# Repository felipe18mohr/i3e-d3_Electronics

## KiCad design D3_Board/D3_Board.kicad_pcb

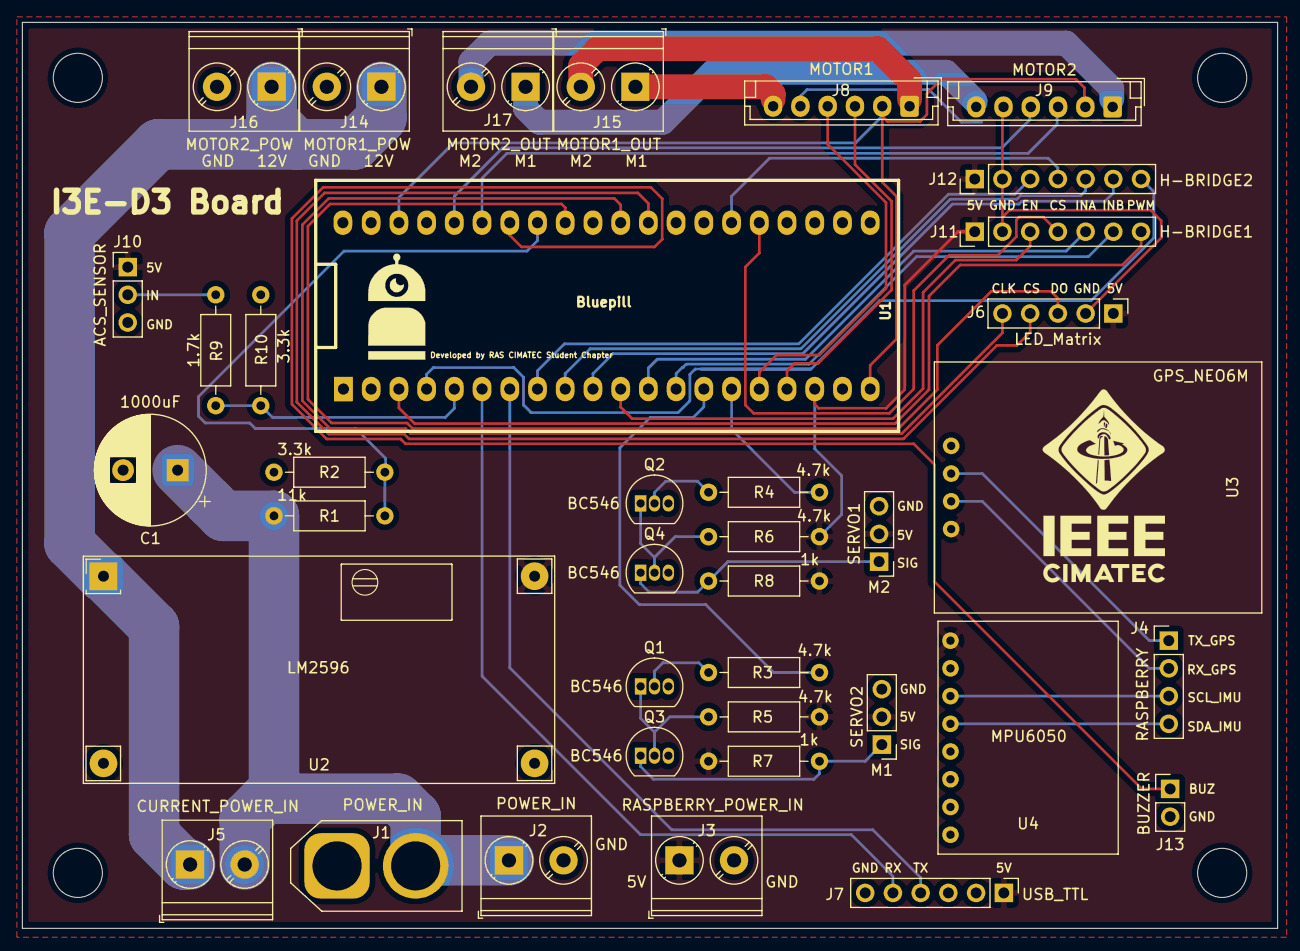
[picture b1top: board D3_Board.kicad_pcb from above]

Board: 2 copper layers, 115.0 x 83.0 mm, 38 parts (0 on the bottom side), 44 nets.

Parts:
C1: 1000uF; CP_Radial_D10.0mm_P5.00mm
J1: POWER_IN; AMASS_XT60-M_1x02_P7.20mm_Vertical
J2: POWER_IN; TerminalBlock_Phoenix_PT-1,5-2-5.0-H_1x02_P5.00mm_Horizontal
J3: RASPBERRY_POWER_IN; TerminalBlock_Phoenix_PT-1,5-2-5.0-H_1x02_P5.00mm_Horizontal
J4: RASPBERRY; PinHeader_1x04_P2.54mm_Vertical
J5: CURRENT_POWER_IN; TerminalBlock_Phoenix_PT-1,5-2-5.0-H_1x02_P5.00mm_Horizontal
J6: LED_Matrix; PinHeader_1x05_P2.54mm_Vertical
J7: USB_TTL; PinHeader_1x06_P2.54mm_Vertical
J8: MOTOR1; JST_EH_B6B-EH-A_1x06_P2.50mm_Vertical
J9: MOTOR2; JST_EH_B6B-EH-A_1x06_P2.50mm_Vertical
J10: ACS_SENSOR; PinHeader_1x03_P2.54mm_Vertical
J11: H-BRIDGE1; PinHeader_1x07_P2.54mm_Vertical
J12: H-BRIDGE2; PinHeader_1x07_P2.54mm_Vertical
J13: BUZZER; PinHeader_1x02_P2.54mm_Vertical
J14: MOTOR1_POW; TerminalBlock_Phoenix_PT-1,5-2-5.0-H_1x02_P5.00mm_Horizontal
J15: MOTOR1_OUT; TerminalBlock_Phoenix_PT-1,5-2-5.0-H_1x02_P5.00mm_Horizontal
J16: MOTOR2_POW; TerminalBlock_Phoenix_PT-1,5-2-5.0-H_1x02_P5.00mm_Horizontal
J17: MOTOR2_OUT; TerminalBlock_Phoenix_PT-1,5-2-5.0-H_1x02_P5.00mm_Horizontal
M1: SERVO2; PinHeader_1x03_P2.54mm_Vertical
M2: SERVO1; PinHeader_1x03_P2.54mm_Vertical
Q1, Q2, Q3, Q4: BC546; TO-92_Inline
R1: 11k; R_Axial_DIN0207_L6.3mm_D2.5mm_P10.16mm_Horizontal
R2, R10: 3.3k; R_Axial_DIN0207_L6.3mm_D2.5mm_P10.16mm_Horizontal
R3, R4, R5, R6: 4.7k; R_Axial_DIN0207_L6.3mm_D2.5mm_P10.16mm_Horizontal
R7, R8: 1k; R_Axial_DIN0207_L6.3mm_D2.5mm_P10.16mm_Horizontal
R9: 1.7k; R_Axial_DIN0207_L6.3mm_D2.5mm_P10.16mm_Horizontal
U1: Bluepill; BluePill_STM32F103C
U2: LM2596; LM2596_module
U3: GPS_NEO6M; GPS_NEO6M_module
U4: MPU6050; MPU6050_module

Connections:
+3V3: J8.2, J9.2, U1.20, U1.38
+5V: J3.1, J6.1, J7.1, J10.1, J11.1, J12.1, M1.2, M2.2, R5.2, R6.2, R7.2, R8.2, U1.18, U2.4, U3.1, U4.1
+12V: J5.1, J14.1, J16.1, U2.1
/ACS: R9.2, R10.1, U1.5
/AVS: R1.2, R2.1, U1.33
/BUZZER: J13.1, U1.34
/CLK_LED: J6.5, U1.30
/CS_LED: J6.4, U1.29
/DOUT_LED: J6.3, U1.32
/ENCODER1_A: J8.4, U1.16
/ENCODER1_B: J8.3, U1.17
/ENCODER2_A: J9.4, U1.36
/ENCODER2_B: J9.3, U1.35
/MOTOR1_CS: J11.4, U1.25
/MOTOR1_EN: J11.3, U1.11
/MOTOR1_INA: J11.5, U1.12
/MOTOR1_INB: J11.6, U1.13
/MOTOR1_M1: J8.6, J15.1
/MOTOR1_M2: J8.1, J15.2
/MOTOR1_PWM: J11.7, U1.3
/MOTOR2_CS: J12.4, U1.26
/MOTOR2_EN: J12.3, U1.8
/MOTOR2_INA: J12.5, U1.9
/MOTOR2_INB: J12.6, U1.10
/MOTOR2_M1: J9.6, J17.1
/MOTOR2_M2: J9.1, J17.2
/MOTOR2_PWM: J12.7, U1.4
/RX_GPS: J4.2, U3.2
/RX_SERIAL: J7.5, U1.6
/SCL: J4.3, U4.3
/SDA: J4.4, U4.4
/SERVO1: R3.2, U1.14
/SERVO2: R4.2, U1.15
/TX_GPS: J4.1, U3.3
/TX_SERIAL: J7.4, U1.7
GND: C1.2, J1.1, J2.2, J3.2, J6.2, J7.6, J8.5, J9.5, J10.3, J11.2, J12.2, J13.2, J14.2, J16.2, M1.3, M2.3, Q1.3, Q2.3, Q3.3, Q4.3, R2.2, R10.2, U1.19, U1.39, U1.40, U2.2, U2.3, U3.4, U4.2
unnamed: C1.1, J1.2, J2.1, J5.2, R1.1
unnamed: J10.2, R9.1
unnamed: M1.1, Q3.1, R7.1
unnamed: M2.1, Q4.1, R8.1
unnamed: Q1.1, Q3.2, R5.1
unnamed: Q1.2, R3.1
unnamed: Q2.1, Q4.2, R6.1
unnamed: Q2.2, R4.1

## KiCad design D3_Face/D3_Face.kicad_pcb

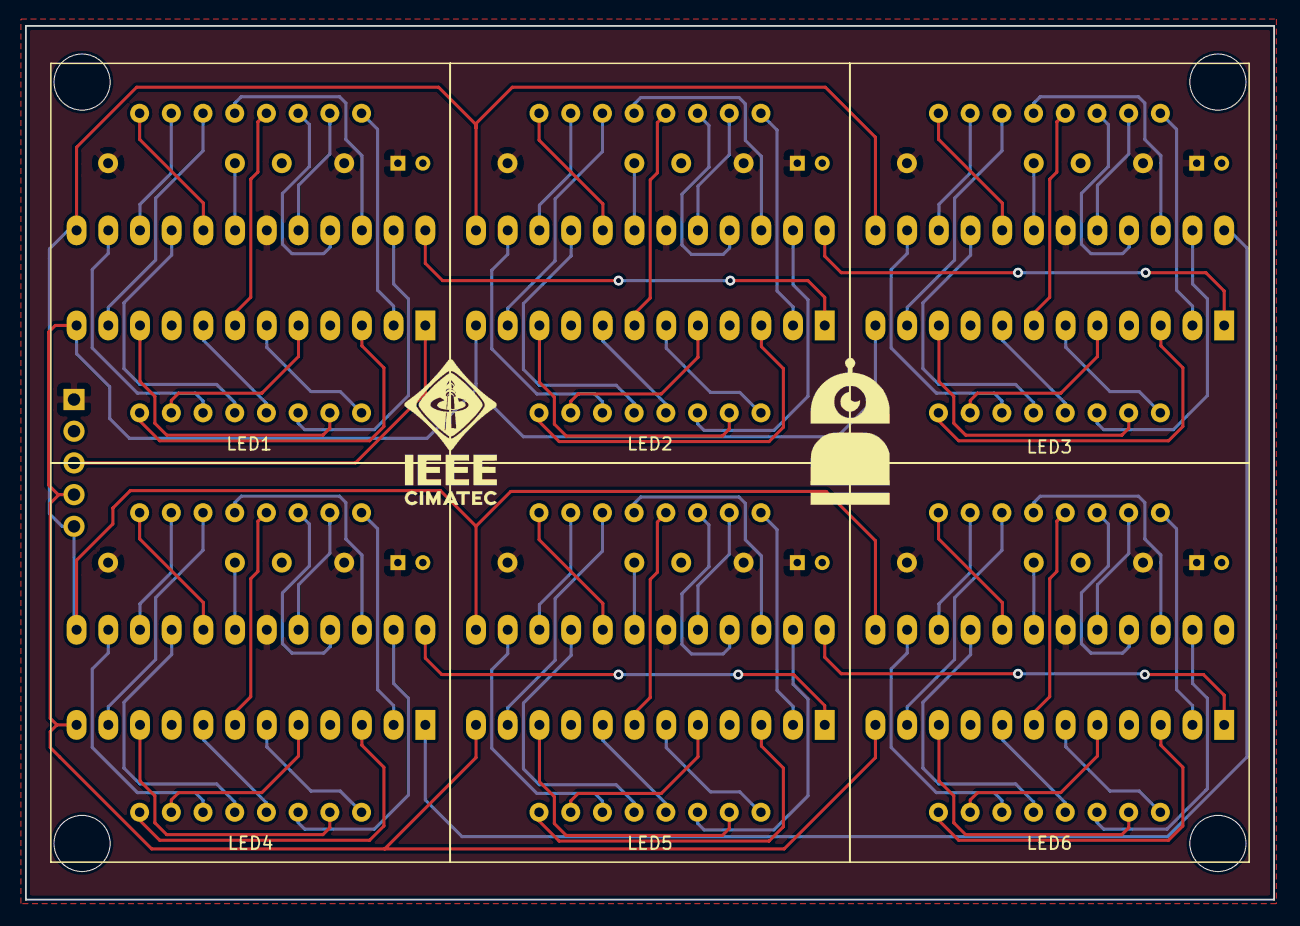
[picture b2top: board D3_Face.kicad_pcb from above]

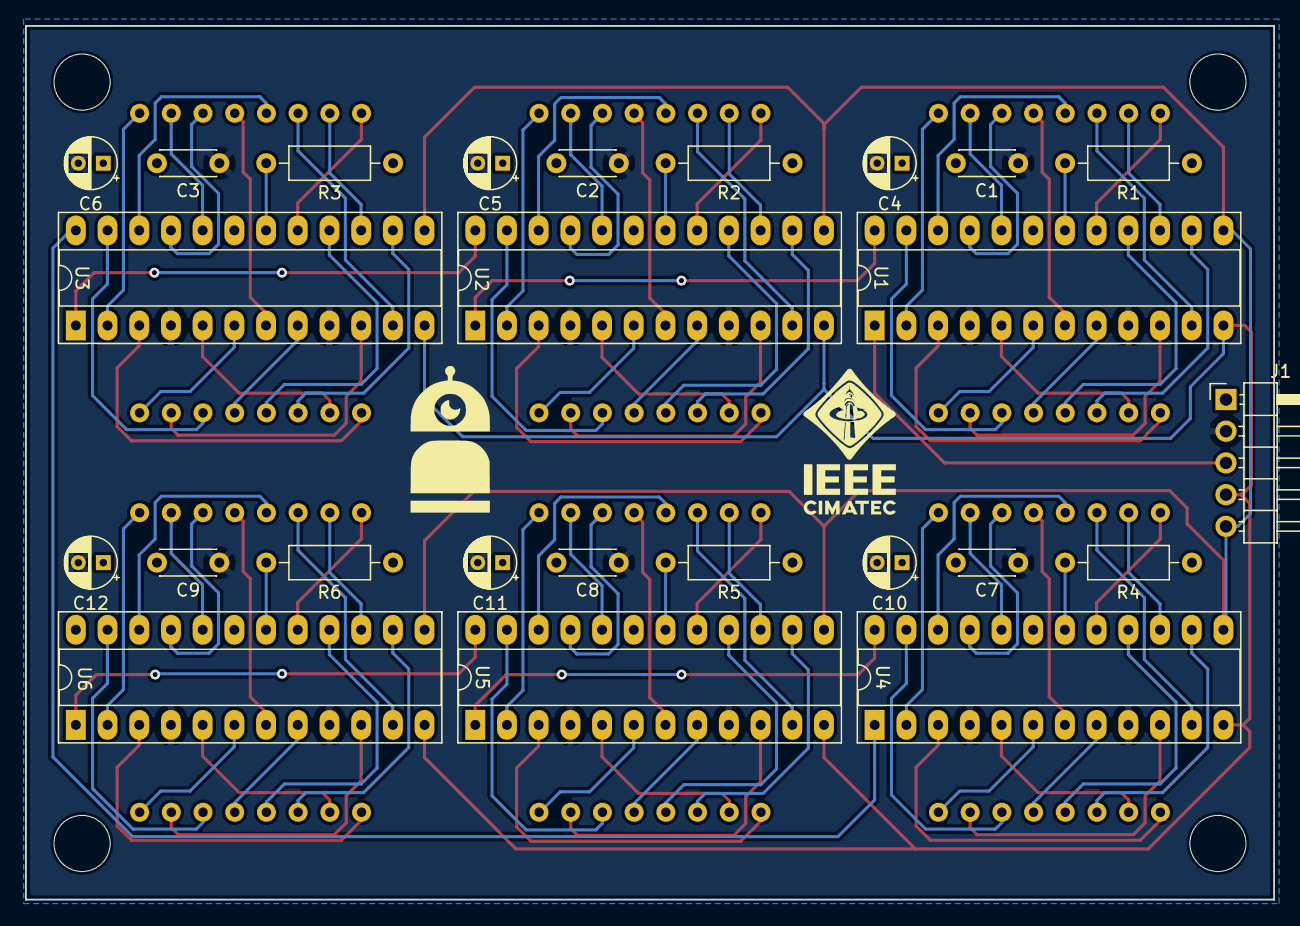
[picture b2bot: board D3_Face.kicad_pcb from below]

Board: 2 copper layers, 100.0 x 70.0 mm, 31 parts (25 on the bottom side), 112 nets.

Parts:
C1, C2, C3, C7, C8, C9: 0.1u; C_Disc_D4.3mm_W1.9mm_P5.00mm
C4, C5, C6, C10, C11, C12: 10u; CP_Radial_D4.0mm_P2.00mm
J1: Conn_01x05_Male; PinHeader_1x05_P2.54mm_Horizontal
LED1, LED2, LED3, LED4, LED5, LED6: Matrix_LED_8x8
R1, R2, R3, R4, R5, R6: 10k; R_Axial_DIN0207_L6.3mm_D2.5mm_P10.16mm_Horizontal
U1, U2, U3, U4, U5, U6: MAX7219; DIP-24_W7.62mm_Socket_LongPads

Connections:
+5V: C1.2, C2.2, C3.2, C4.1, C5.1, C6.1, C7.2, C8.2, C9.2, C10.1, C11.1, C12.1, J1.1, R1.1, R2.1, R3.1, R4.1, R5.1, R6.1, U1.19, U2.19, U3.19, U4.19, U5.19, U6.19
CLK: J1.5, U1.13, U2.13, U3.13, U4.13, U5.13, U6.13
CS: J1.4, U1.12, U2.12, U3.12, U4.12, U5.12, U6.12
GND: C1.1, C2.1, C3.1, C4.2, C5.2, C6.2, C7.1, C8.1, C9.1, C10.2, C11.2, C12.2, J1.2, U1.4, U1.9, U2.4, U2.9, U3.4, U3.9, U4.4, U4.9, U5.4, U5.9, U6.4, U6.9
unnamed: J1.3, U1.1
unnamed: LED1.1, U1.3
unnamed: LED1.2, U1.5
unnamed: LED1.3, U1.14
unnamed: LED1.4, U1.16
unnamed: LED1.5, U1.8
unnamed: LED1.6, U1.23
unnamed: LED1.7, U1.10
unnamed: LED1.8, U1.6
unnamed: LED1.9, U1.2
unnamed: LED1.10, U1.20
unnamed: LED1.11, U1.21
unnamed: LED1.12, U1.7
unnamed: LED1.13, U1.22
unnamed: LED1.14, U1.11
unnamed: LED1.15, U1.15
unnamed: LED1.16, U1.17
unnamed: LED2.1, U2.3
unnamed: LED2.2, U2.5
unnamed: LED2.3, U2.14
unnamed: LED2.4, U2.16
unnamed: LED2.5, U2.8
unnamed: LED2.6, U2.23
unnamed: LED2.7, U2.10
unnamed: LED2.8, U2.6
unnamed: LED2.9, U2.2
unnamed: LED2.10, U2.20
unnamed: LED2.11, U2.21
unnamed: LED2.12, U2.7
unnamed: LED2.13, U2.22
unnamed: LED2.14, U2.11
unnamed: LED2.15, U2.15
unnamed: LED2.16, U2.17
unnamed: LED3.1, U3.3
unnamed: LED3.2, U3.5
unnamed: LED3.3, U3.14
unnamed: LED3.4, U3.16
unnamed: LED3.5, U3.8
unnamed: LED3.6, U3.23
unnamed: LED3.7, U3.10
unnamed: LED3.8, U3.6
unnamed: LED3.9, U3.2
unnamed: LED3.10, U3.20
unnamed: LED3.11, U3.21
unnamed: LED3.12, U3.7
unnamed: LED3.13, U3.22
unnamed: LED3.14, U3.11
unnamed: LED3.15, U3.15
unnamed: LED3.16, U3.17
unnamed: LED4.1, U4.3
unnamed: LED4.2, U4.5
unnamed: LED4.3, U4.14
unnamed: LED4.4, U4.16
unnamed: LED4.5, U4.8
unnamed: LED4.6, U4.23
unnamed: LED4.7, U4.10
unnamed: LED4.8, U4.6
unnamed: LED4.9, U4.2
unnamed: LED4.10, U4.20
unnamed: LED4.11, U4.21
unnamed: LED4.12, U4.7
unnamed: LED4.13, U4.22
unnamed: LED4.14, U4.11
unnamed: LED4.15, U4.15
unnamed: LED4.16, U4.17
unnamed: LED5.1, U5.3
unnamed: LED5.2, U5.5
unnamed: LED5.3, U5.14
unnamed: LED5.4, U5.16
unnamed: LED5.5, U5.8
unnamed: LED5.6, U5.23
unnamed: LED5.7, U5.10
unnamed: LED5.8, U5.6
unnamed: LED5.9, U5.2
unnamed: LED5.10, U5.20
unnamed: LED5.11, U5.21
unnamed: LED5.12, U5.7
unnamed: LED5.13, U5.22
unnamed: LED5.14, U5.11
unnamed: LED5.15, U5.15
unnamed: LED5.16, U5.17
unnamed: LED6.1, U6.3
unnamed: LED6.2, U6.5
unnamed: LED6.3, U6.14
unnamed: LED6.4, U6.16
unnamed: LED6.5, U6.8
unnamed: LED6.6, U6.23
unnamed: LED6.7, U6.10
unnamed: LED6.8, U6.6
unnamed: LED6.9, U6.2
unnamed: LED6.10, U6.20
unnamed: LED6.11, U6.21
unnamed: LED6.12, U6.7
unnamed: LED6.13, U6.22
unnamed: LED6.14, U6.11
unnamed: LED6.15, U6.15
unnamed: LED6.16, U6.17
unnamed: R1.2, U1.18
unnamed: R2.2, U2.18
unnamed: R3.2, U3.18
unnamed: R4.2, U4.18
unnamed: R5.2, U5.18
unnamed: R6.2, U6.18
unnamed: U1.24, U2.1
unnamed: U2.24, U3.1
unnamed: U3.24, U4.1
unnamed: U4.24, U5.1
unnamed: U5.24, U6.1

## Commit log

2021-01-19 finish Face PCB traces
2021-02-11 Create D3_Board
2021-02-16 Board inprog
2021-02-21 Add connections
2021-02-24 Finish schematics
2021-04-24 PCB Layout inprog
2021-04-25 Finish traces
2021-04-25 Finish PCBs
2021-04-25 Add 3d models and README
2021-05-10 Update main board Schematics
2021-07-14 Create simple board
